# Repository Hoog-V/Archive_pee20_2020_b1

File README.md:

**Repository voor het robotproject**

---

## Schematische tekeningen

De schematische tekeningen voor de units en het volledige project is te vinden in de map: [schematische-tekeningen](https://bitbucket.org/HR_ELE_STUD/pee20_2020_b1/src/master/schematische-tekeningen/).
Hierin staan ook de bestanden van de printplaat.

---

## Deelprogramma's

Naast de volledige integratie V2 zijn er ook deelprogramma's die bepaalde functies van de robot in code implementeren. Deze deelprogramma's komen
in zijn volledigheid of deels voor in de volledige integratie V2. **Sommige van deze deelprogramma's kunnen afwijken van de code gebruikt in de Volledige Integratie V2**.
De deelprogramma's zijn:

1). [Botsdetectie](https://bitbucket.org/HR_ELE_STUD/pee20_2020_b1/src/master/Deelprogramma's%20onderdelen/Botsdetectie/)   

2). [Interfaces](https://bitbucket.org/HR_ELE_STUD/pee20_2020_b1/src/master/Deelprogramma's%20onderdelen/Interfaces/)  

3). [Motorbesturing](https://bitbucket.org/HR_ELE_STUD/pee20_2020_b1/src/master/Deelprogramma's%20onderdelen/)              

4). [Lijn volger](https://bitbucket.org/HR_ELE_STUD/pee20_2020_b1/src/master/Deelprogramma's%20onderdelen/)                

5). [NFC lezer](https://bitbucket.org/HR_ELE_STUD/pee20_2020_b1/src/master/Deelprogramma's%20onderdelen/)	            

Alles is af. De acceptatietest is bij de herkansing met een voldoende afgerond. De code is te vinden in de map [Volledige Integratie V2](https://bitbucket.org/HR_ELE_STUD/pee20_2020_b1/src/master/Deelprogramma's%20onderdelen/Volledige%20Integratie%20V2/). 
In deze map is de code as-build ingeleverd.

---

## Eindrevisie

De eindrevisie van de code die is ingeleverd na de acceptatietest staat in de map: [Volledige Integratie V2](https://bitbucket.org/HR_ELE_STUD/pee20_2020_b1/src/master/Deelprogramma's%20onderdelen/Volledige%20Integratie%20V2/). 
Of als u het handmatig wilt opzoeken: Deelprogramma's onderdelen -> Volledige Integratie V2.

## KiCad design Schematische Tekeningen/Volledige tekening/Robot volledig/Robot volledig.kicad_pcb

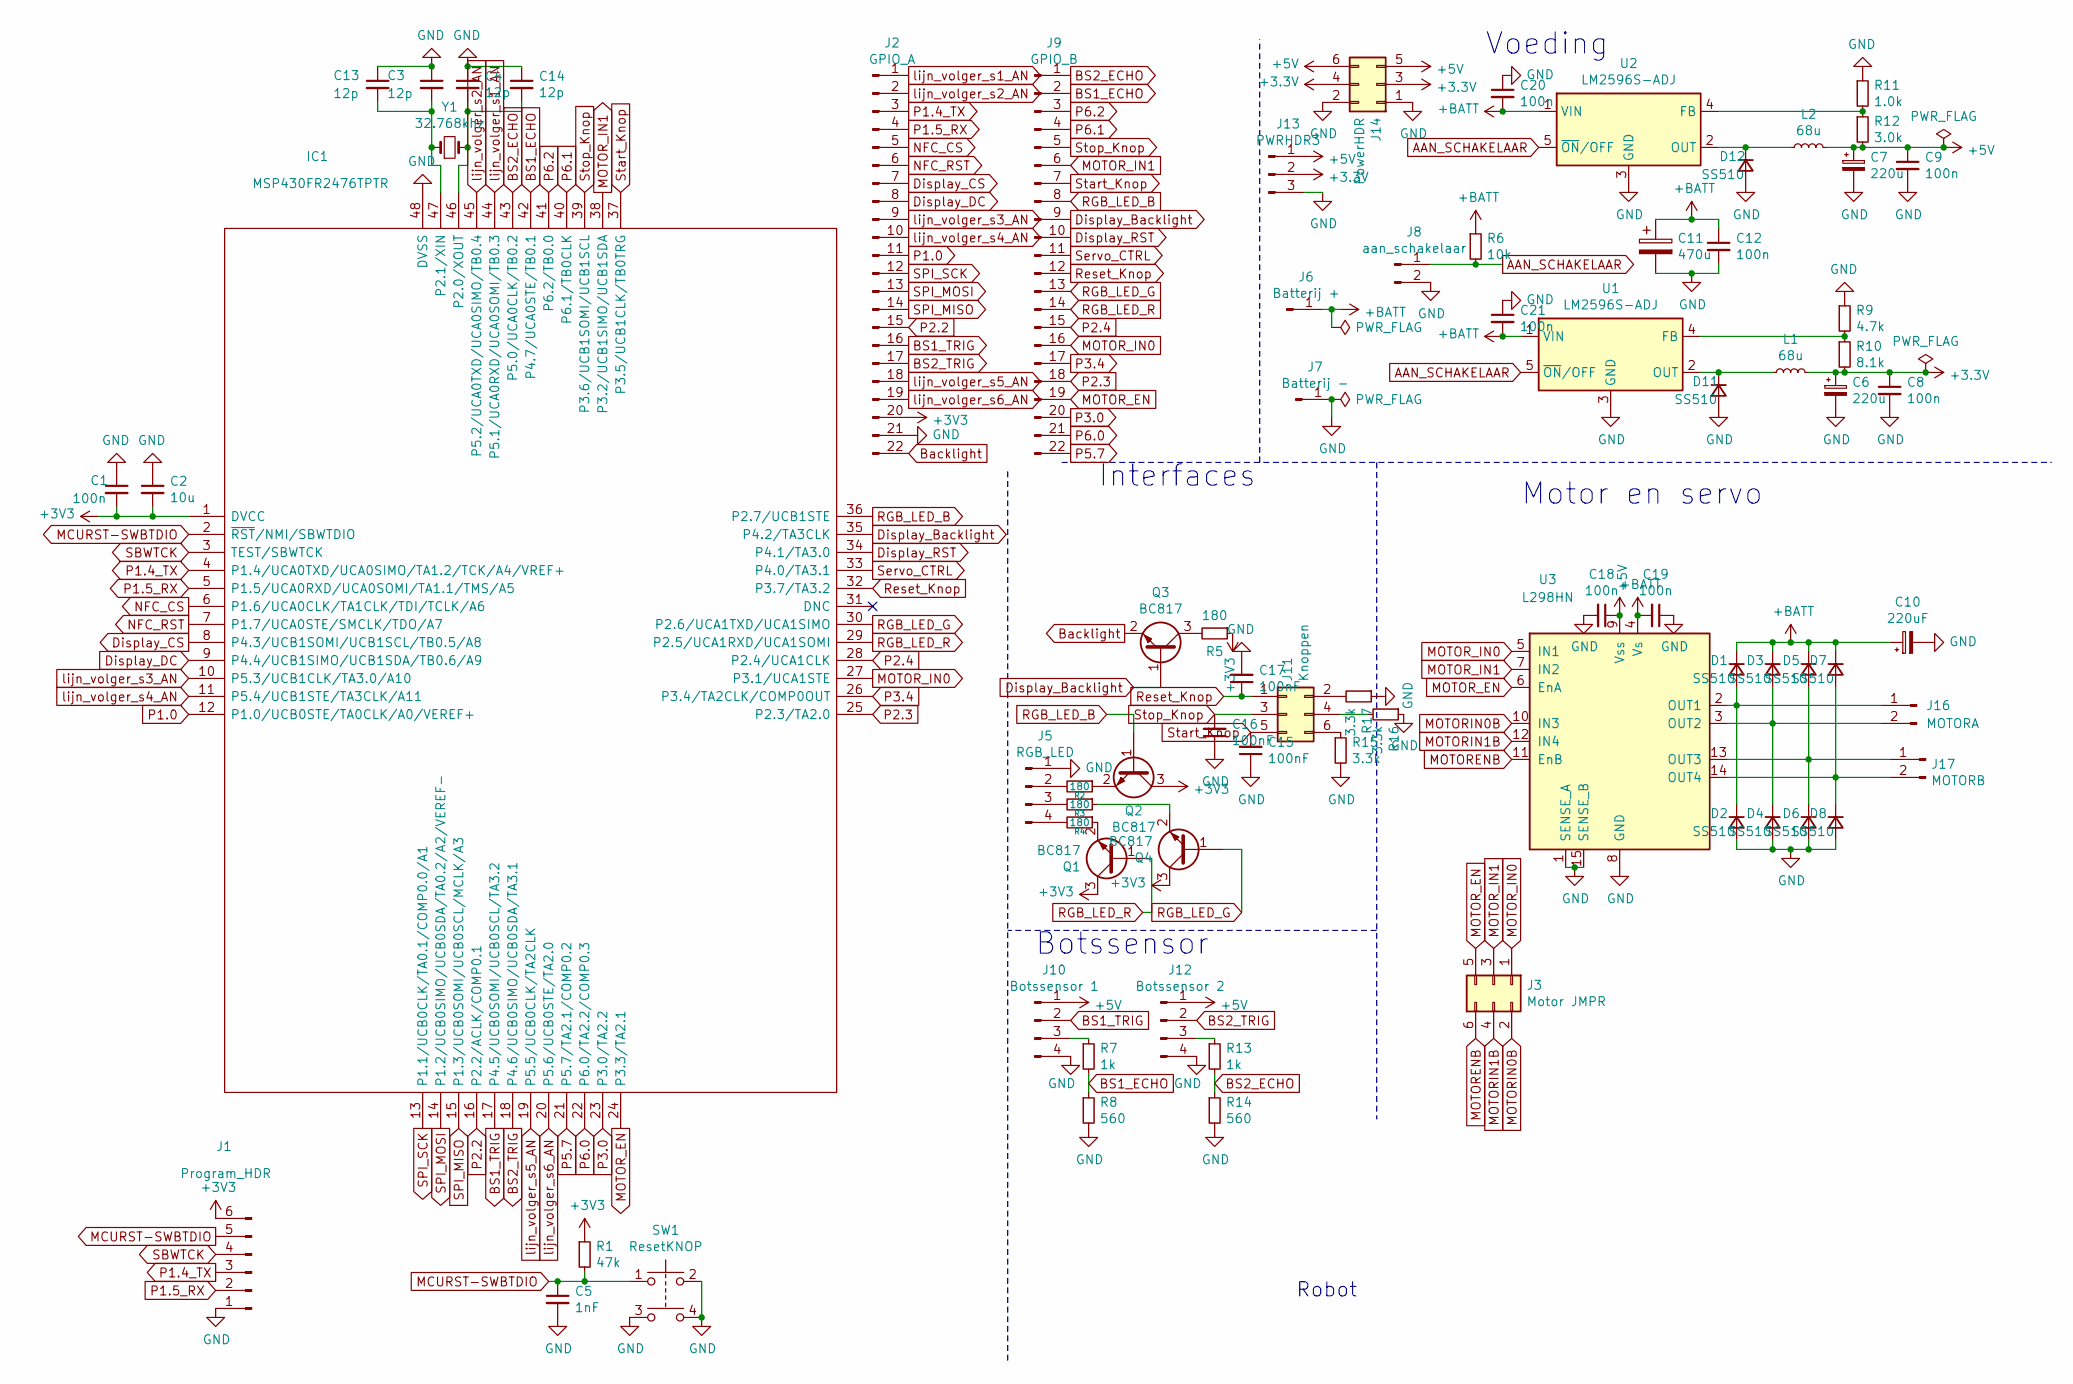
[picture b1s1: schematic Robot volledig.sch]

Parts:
C1, C8, C9, C12, C18, C19, C20, C21: 100n; C_0603_1608Metric_Pad1.08x0.95mm_HandSolder
C2: 10u; C_0603_1608Metric_Pad1.08x0.95mm_HandSolder
C3, C4: 12p; C_0201_0603Metric_Pad0.64x0.40mm_HandSolder
C5: 1nF; C_0603_1608Metric_Pad1.08x0.95mm_HandSolder
C6, C7: 220u; CP_Radial_D10.0mm_P5.00mm
C10: 220uF; CP_Radial_D10.0mm_P5.00mm
C11: 470u; CP_Radial_D10.0mm_P5.00mm
C13, C14: 12p; C_0603_1608Metric_Pad1.08x0.95mm_HandSolder
C15, C16, C17: 100nF; C_0603_1608Metric_Pad1.08x0.95mm_HandSolder
D1, D2, D3, D4, D5, D6, D7, D8, D11, D12: SS510; D_SMB_Handsoldering
IC1: MSP430FR2476TPTR; QFP50P900X900X160-48N; Mouser Part Number 595-MSP430FR2476TPTR
J1: Program_HDR; PinHeader_1x06_P2.54mm_Vertical
J2: GPIO_A; PinHeader_1x22_P2.54mm_Vertical
J3: Motor JMPR; PinHeader_2x03_P2.54mm_Vertical
J5: RGB_LED; PinHeader_1x04_P2.54mm_Vertical
J6: Batterij +; Pin_D1.4mm_L8.5mm_W2.8mm_FlatFork
J7: Batterij -; Pin_D1.4mm_L8.5mm_W2.8mm_FlatFork
J8: aan_schakelaar; PinHeader_1x02_P2.54mm_Vertical
J9: GPIO_B; PinHeader_1x22_P2.54mm_Vertical
J10: Botssensor 1; PinHeader_1x04_P2.54mm_Vertical
J11: Knoppen; PinHeader_2x03_P2.54mm_Vertical
J12: Botssensor 2; PinHeader_1x04_P2.54mm_Vertical
J13: PWRHDR3; PinHeader_1x03_P2.54mm_Vertical
J14: PowerHDR; PinHeader_2x03_P2.54mm_Vertical
J16: MOTORA; PinHeader_1x02_P2.54mm_Vertical
J17: MOTORB; PinHeader_1x02_P2.54mm_Vertical
L1, L2: 68u; L_10.4x10.4_H4.8
Q1, Q2, Q3, Q4: BC817; SOT-23
R1: 47k; R_0603_1608Metric_Pad0.98x0.95mm_HandSolder
R2, R3, R4, R5: 180; R_0603_1608Metric_Pad0.98x0.95mm_HandSolder
R6: 10k; R_0603_1608Metric_Pad0.98x0.95mm_HandSolder
R7, R13: 1k; R_0603_1608Metric_Pad0.98x0.95mm_HandSolder
R8, R14: 560; R_0603_1608Metric_Pad0.98x0.95mm_HandSolder
R9: 4.7k; R_0603_1608Metric_Pad0.98x0.95mm_HandSolder
R10: 8.1k; R_0603_1608Metric_Pad0.98x0.95mm_HandSolder
R11: 1.0k; R_0603_1608Metric_Pad0.98x0.95mm_HandSolder
R12: 3.0k; R_0603_1608Metric_Pad0.98x0.95mm_HandSolder
R15, R16, R17: 3.3k; R_0603_1608Metric_Pad0.98x0.95mm_HandSolder
SW1: ResetKNOP; SW_SPST_B3S-1000
U1, U2: LM2596S-ADJ; TO-263-5_TabPin3
U3: L298HN; TO-220-15_P2.54x2.54mm_StaggerOdd_Lead4.58mm_Vertical
Y1: 32.768khz; Crystal_SMD_3215-2Pin_3.2x1.5mm

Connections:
+5V: C7.1, C9.1, C18.1, J10.1, J12.1, J13.1, J14.5, J14.6, L2.2, R12.2, U3.9 (Vss)
+BATT: C10.1, C11.1, C12.1, C19.2, C20.2, C21.2, D1.1 (K), D3.1 (K), D5.1 (K), D7.1 (K), J6.1, R6.1, U1.1 (VIN), U2.1 (VIN), U3.4 (Vs)
AAN_SCHAKELAAR: J8.1, R6.2, U1.5 (~ON~/OFF), U2.5 (~ON~/OFF)
BS1_ECHO: IC1.42 (P4.7/UCA0STE/TB0.1), J9.2, R7.2, R8.1
BS1_TRIG: IC1.17 (P4.5/UCB0SOMI/UCB0SCL/TA3.2), J2.16, J10.2
BS2_ECHO: IC1.43 (P5.0/UCA0CLK/TB0.2), J9.1, R13.2, R14.1
BS2_TRIG: IC1.18 (P4.6/UCB0SIMO/UCB0SDA/TA3.1), J2.17, J12.2
Backlight: J2.22, Q3.2 (E)
Display_Backlight: IC1.35 (P4.2/TA3CLK), J9.9, Q3.1 (B)
Display_CS: IC1.8 (P4.3/UCB1SOMI/UCB1SCL/TB0.5/A8), J2.7
Display_DC: IC1.9 (P4.4/UCB1SIMO/UCB1SDA/TB0.6/A9), J2.8
Display_RST: IC1.34 (P4.1/TA3.0), J9.10
GND: C1.1, C2.1, C3.1, C4.1, C5.2, C6.2, C7.2, C8.2, C9.2, C10.2, C11.2, C12.2, C13.1, C14.1, C15.1, C16.1, C17.2, C18.2, C19.1, C20.1, C21.1, D2.2 (A), D4.2 (A), D6.2 (A), D8.2 (A), D11.2 (A), D12.2 (A), IC1.48 (DVSS), J1.1, J2.21, J5.1, J7.1, J8.2, J10.4, J12.4, J13.3, J14.1, J14.2, R8.2, R9.1, R11.1, R14.2, R15.2, R16.1, R17.1, SW1.2, SW1.3, SW1.4, U1.3 (GND), U2.3 (GND), U3.1 (SENSE_A), U3.8 (GND), U3.15 (SENSE_B)
MCURST-SWBTDIO: C5.1, IC1.2 (~RST~/NMI/SBWTDIO), J1.5, R1.2, SW1.1
MOTORENB: J3.6, U3.11 (EnB)
MOTORIN0B: J3.2, U3.10 (IN3)
MOTORIN1B: J3.4, U3.12 (IN4)
MOTOR_EN: IC1.24 (P3.3/TA2.1), J3.5, J9.19, U3.6 (EnA)
MOTOR_IN0: IC1.27 (P3.1/UCA1STE), J3.1, J9.16, U3.5 (IN1)
MOTOR_IN1: IC1.38 (P3.2/UCB1SIMO/UCB1SDA), J3.3, J9.6, U3.7 (IN2)
NFC_CS: IC1.6 (P1.6/UCA0CLK/TA1CLK/TDI/TCLK/A6), J2.5
NFC_RST: IC1.7 (P1.7/UCA0STE/SMCLK/TDO/A7), J2.6
unnamed: C3.2, C13.2, IC1.47 (P2.1/XIN), Y1.1
unnamed: C4.2, C14.2, IC1.46 (P2.0/XOUT), Y1.2
unnamed: D1.2 (A), D2.1 (K), J16.1, U3.2 (OUT1)
unnamed: D3.2 (A), D4.1 (K), J16.2, U3.3 (OUT2)
unnamed: D5.2 (A), D6.1 (K), J17.1, U3.13 (OUT3)
unnamed: D7.2 (A), D8.1 (K), J17.2, U3.14 (OUT4)
unnamed: D11.1 (K), L1.1, U1.2 (OUT)
unnamed: D12.1 (K), L2.1, U2.2 (OUT)
unnamed: J5.2, R2.2
unnamed: J5.3, R3.2
unnamed: J5.4, R4.2
unnamed: J10.3, R7.1
unnamed: J11.2, R17.2
unnamed: J11.4, R16.2
unnamed: J11.6, R15.1
unnamed: J12.3, R13.1
unnamed: Q1.2 (E), R4.1
unnamed: Q2.2 (E), R2.1
unnamed: Q3.3 (C), R5.2
unnamed: Q4.2 (E), R3.1
unnamed: R9.2, R10.1, U1.4 (FB)
unnamed: R11.2, R12.1, U2.4 (FB)
P1.0: IC1.12 (P1.0/UCB0STE/TA0CLK/A0/VEREF+), J2.11
P1.4_TX: IC1.4 (P1.4/UCA0TXD/UCA0SIMO/TA1.2/TCK/A4/VREF+), J1.3, J2.3
P1.5_RX: IC1.5 (P1.5/UCA0RXD/UCA0SOMI/TA1.1/TMS/A5), J1.2, J2.4
P2.2: IC1.16 (P2.2/ACLK/COMP0.1), J2.15
P2.3: IC1.25 (P2.3/TA2.0), J9.18
P2.4: IC1.28 (P2.4/UCA1CLK), J9.15
P3.0: IC1.23 (P3.0/TA2.2), J9.20
P3.4: IC1.26 (P3.4/TA2CLK/COMP0OUT), J9.17
P5.7: IC1.21 (P5.7/TA2.1/COMP0.2), J9.22
P6.0: IC1.22 (P6.0/TA2.2/COMP0.3), J9.21
P6.1: IC1.40 (P6.1/TB0CLK), J9.4
P6.2: IC1.41 (P6.2/TB0.0), J9.3
RGB_LED_B: IC1.36 (P2.7/UCB1STE), J9.8, Q2.1 (B)
RGB_LED_G: IC1.30 (P2.6/UCA1TXD/UCA1SIMO), J9.13, Q4.1 (B)
RGB_LED_R: IC1.29 (P2.5/UCA1RXD/UCA1SOMI), J9.14, Q1.1 (B)
Reset_Knop: C17.1, IC1.32 (P3.7/TA3.2), J9.12, J11.1
SBWTCK: IC1.3 (TEST/SBWTCK), J1.4
SPI_MISO: IC1.15 (P1.3/UCB0SOMI/UCB0SCL/MCLK/A3), J2.14
SPI_MOSI: IC1.14 (P1.2/UCB0SIMO/UCB0SDA/TA0.2/A2/VEREF-), J2.13
SPI_SCK: IC1.13 (P1.1/UCB0CLK/TA0.1/COMP0.0/A1), J2.12
Servo_CTRL: IC1.33 (P4.0/TA3.1), J9.11
Start_Knop: C15.2, IC1.37 (P3.5/UCB1CLK/TB0TRG), J9.7, J11.5
Stop_Knop: C16.2, IC1.39 (P3.6/UCB1SOMI/UCB1SCL), J9.5, J11.3
lijn_volger_s1_AN: IC1.44 (P5.1/UCA0RXD/UCA0SOMI/TB0.3), J2.1
lijn_volger_s2_AN: IC1.45 (P5.2/UCA0TXD/UCA0SIMO/TB0.4), J2.2
lijn_volger_s3_AN: IC1.10 (P5.3/UCB1CLK/TA3.0/A10), J2.9
lijn_volger_s4_AN: IC1.11 (P5.4/UCB1STE/TA3CLK/A11), J2.10
lijn_volger_s5_AN: IC1.19 (P5.5/UCB0CLK/TA2CLK), J2.18
lijn_volger_s6_AN: IC1.20 (P5.6/UCB0STE/TA2.0), J2.19

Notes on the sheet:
Robot
Botssensor
Interfaces
Motor en servo
Voeding

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
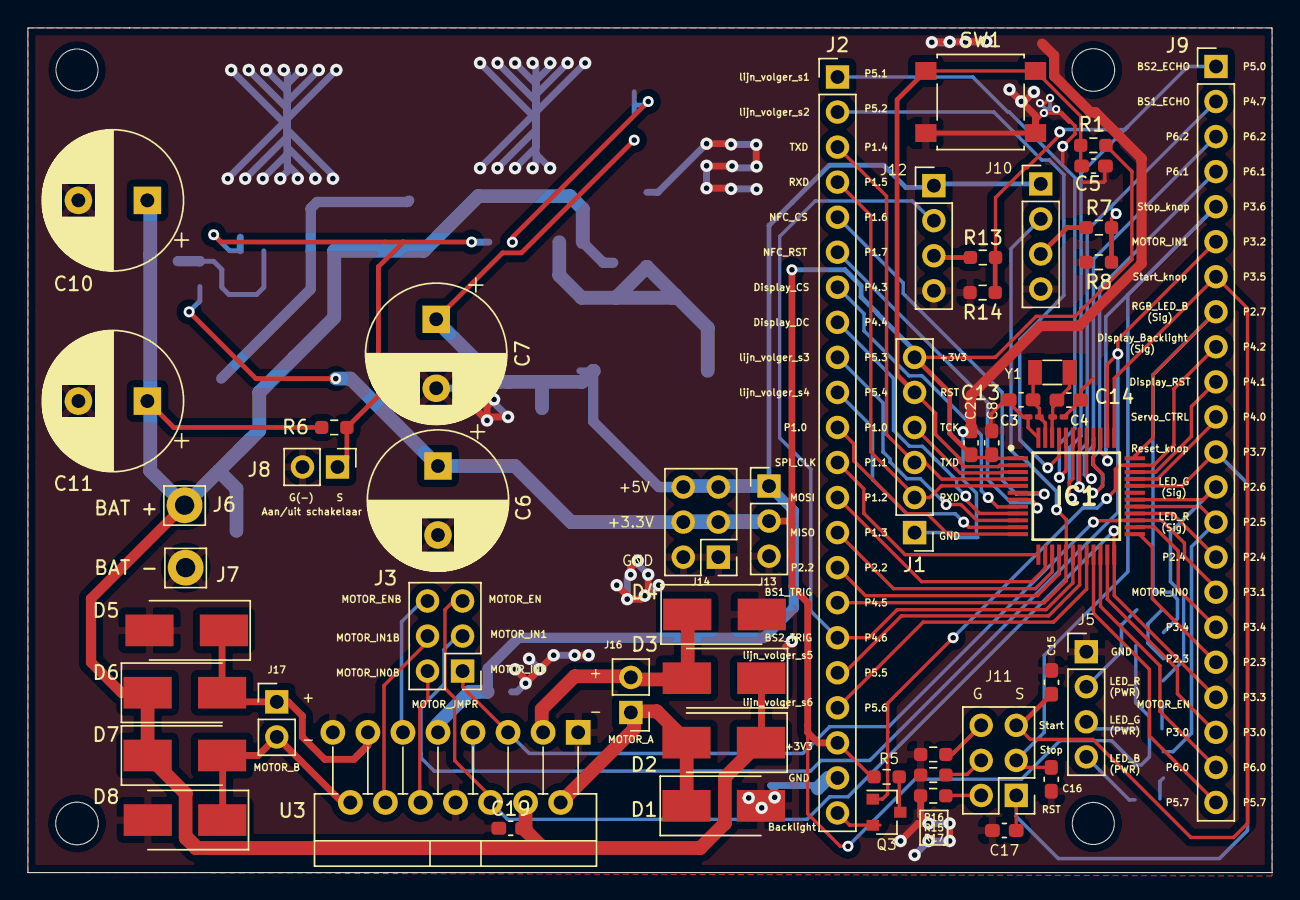
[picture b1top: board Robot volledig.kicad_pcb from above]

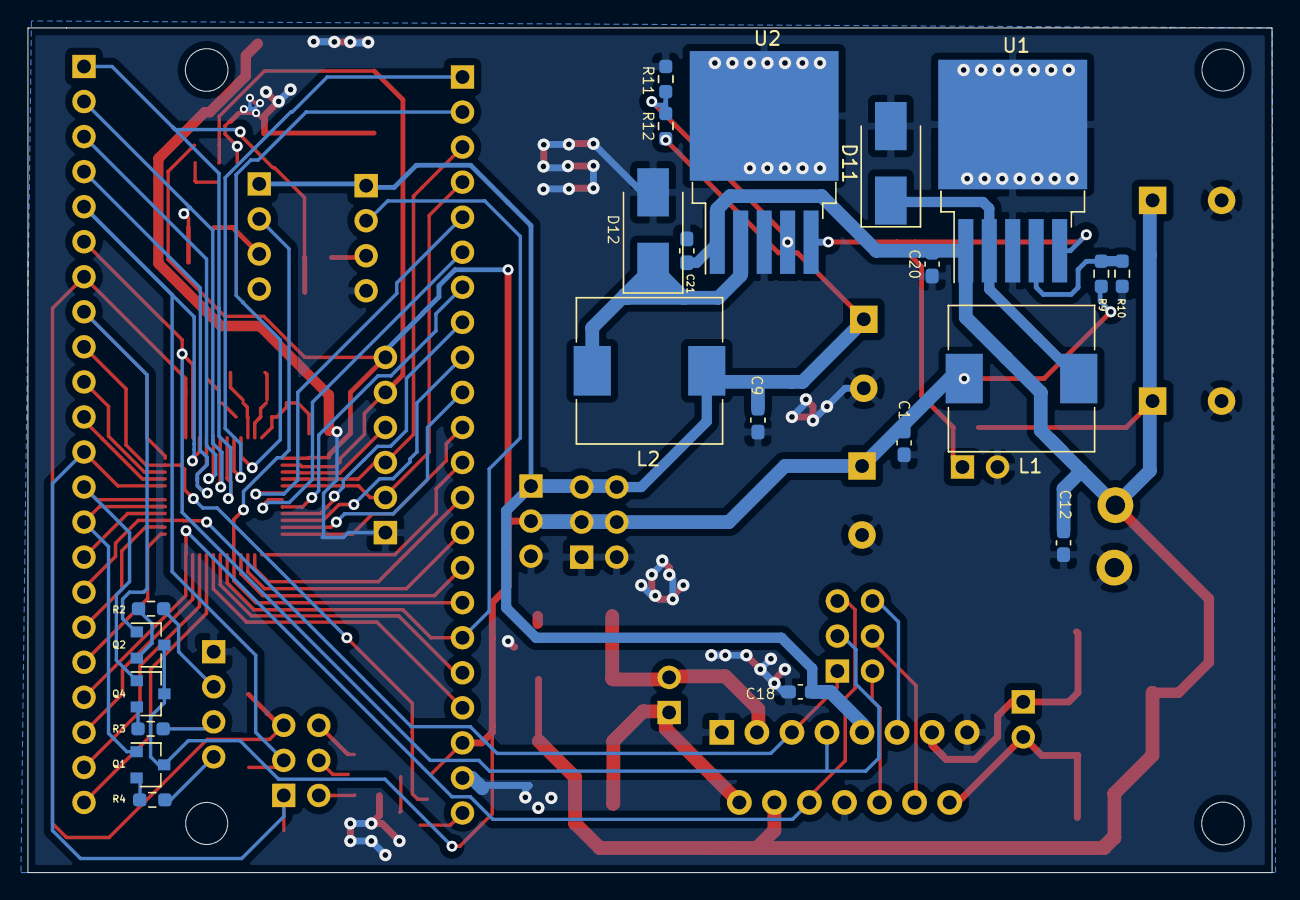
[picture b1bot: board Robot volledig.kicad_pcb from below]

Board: 2 copper layers, 90.2 x 61.2 mm, 75 parts (22 on the bottom side), 74 nets.

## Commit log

2023-03-10 -add old project from bitbucket
